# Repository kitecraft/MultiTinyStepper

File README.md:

# MCPStepper
PCB and Arduino library to control 4 unipolar stepper motors (28BYJ-48 typical)

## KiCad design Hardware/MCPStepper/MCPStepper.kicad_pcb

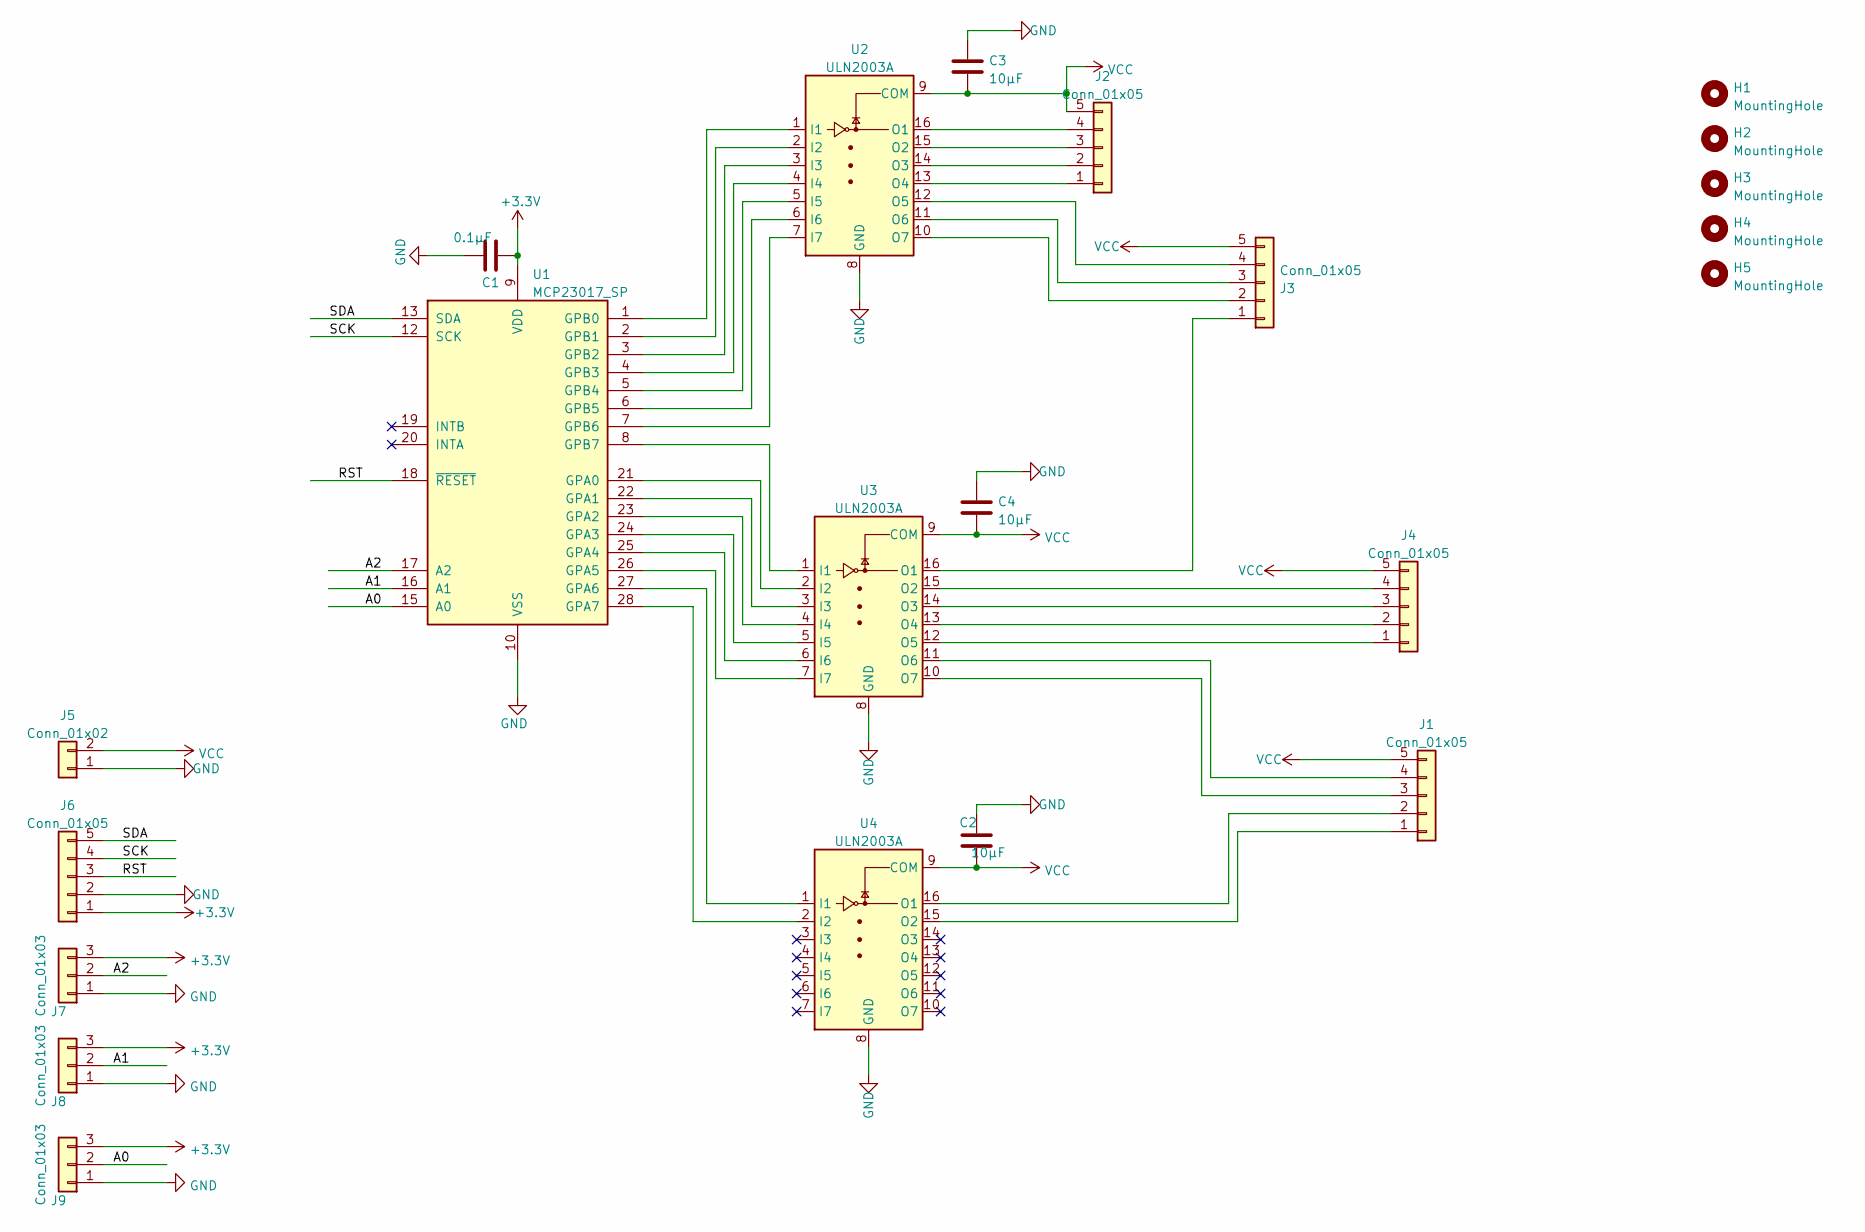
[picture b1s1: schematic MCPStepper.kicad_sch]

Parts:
C1: 0.1µF; C_Disc_D5.0mm_W2.5mm_P2.50mm
C2, C3, C4: 10µF; C_Disc_D5.0mm_W2.5mm_P2.50mm
H1, H2, H3, H4, H5: MountingHole; MountingHole_2.7mm
J1, J2, J3, J4: Conn_01x05; JST_XH_B5B-XH-A_1x05_P2.50mm_Vertical
J5: Conn_01x02; PinHeader_1x02_P2.54_Friction_Lock
J6: Conn_01x05; PinHeader_1x05_P2.54mm_Vertical
J7, J8, J9: Conn_01x03; PinHeader_1x03_P2.54mm_Vertical
U1: MCP23017_SP; DIP-28_W7.62mm_WithSocket
U2, U3, U4: ULN2003A; ULN2003 on Socket

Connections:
+3V3: C1.2, J6.1, J7.3, J8.3, J9.3, U1.9 (VDD)
/A0: J9.2, U1.15 (A0)
/A1: J8.2, U1.16 (A1)
/A2: J7.2, U1.17 (A2)
/RST: J6.3, U1.18 (~RESET)
/SCK: J6.4, U1.12 (SCK)
/SDA: J6.5, U1.13 (SDA)
GND: C1.1, C2.1, C3.1, C4.1, J5.1, J6.2, J7.1, J8.1, J9.1, U1.10 (VSS), U2.8 (GND), U3.8 (GND), U4.8 (GND)
unnamed: J3.1, U3.16 (O1)
unnamed: J3.2, U2.10 (O7)
unnamed: J3.3, U2.11 (O6)
unnamed: J3.4, U2.12 (O5)
unnamed: U1.1 (GPB0), U2.1 (I1)
unnamed: U1.2 (GPB1), U2.2 (I2)
unnamed: U1.3 (GPB2), U2.3 (I3)
unnamed: U1.4 (GPB3), U2.4 (I4)
unnamed: U1.5 (GPB4), U2.5 (I5)
unnamed: U1.6 (GPB5), U2.6 (I6)
unnamed: U1.7 (GPB6), U2.7 (I7)
unnamed: U1.8 (GPB7), U3.1 (I1)
unnamed: U1.21 (GPA0), U3.2 (I2)
unnamed: U1.22 (GPA1), U3.3 (I3)
unnamed: U1.23 (GPA2), U3.4 (I4)
unnamed: U1.24 (GPA3), U3.5 (I5)
unnamed: U1.25 (GPA4), U3.6 (I6)
unnamed: U1.26 (GPA5), U3.7 (I7)
unnamed: U1.27 (GPA6), U4.1 (I1)
unnamed: U1.28 (GPA7), U4.2 (I2)
unnamed: J2.1, U2.13 (O4)
unnamed: J2.2, U2.14 (O3)
unnamed: J2.3, U2.15 (O2)
unnamed: J2.4, U2.16 (O1)
unnamed: J1.3, U3.10 (O7)
unnamed: J1.4, U3.11 (O6)
unnamed: J4.1, U3.12 (O5)
unnamed: J4.2, U3.13 (O4)
unnamed: J4.3, U3.14 (O3)
unnamed: J4.4, U3.15 (O2)
unnamed: J1.1, U4.15 (O2)
unnamed: J1.2, U4.16 (O1)
VCC: C2.2, C3.2, C4.2, J1.5, J2.5, J3.5, J4.5, J5.2, U2.9 (COM), U3.9 (COM), U4.9 (COM)

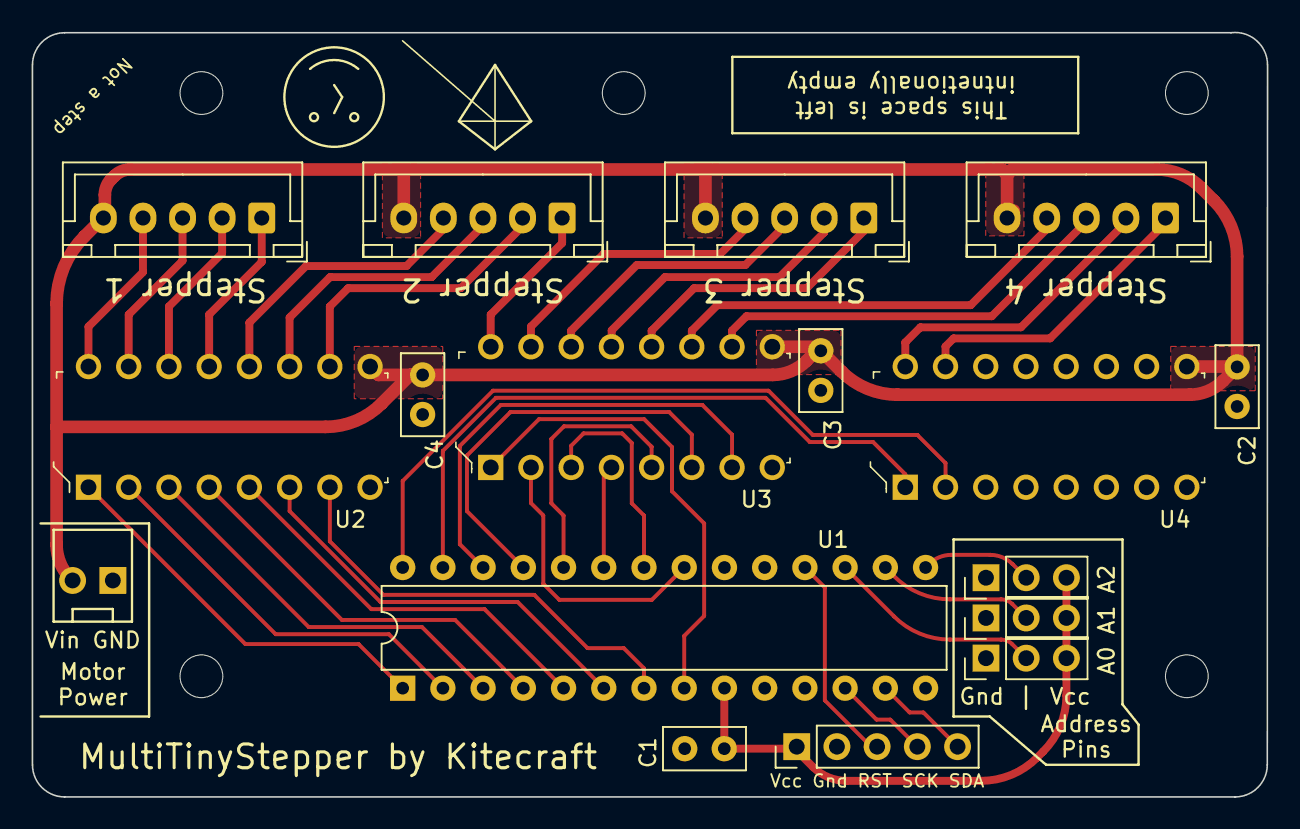
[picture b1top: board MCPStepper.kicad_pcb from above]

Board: 2 copper layers, 78.0 x 48.3 mm, 22 parts (0 on the bottom side), 41 nets.

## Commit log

2022-09-24 Initial hardware commit
2022-12-07 Many updates
2022-12-08 Much progress achieved.
2022-12-08 Updated the PCB
2022-12-09 Fixed bug for half stepping
2022-12-10 Working system.
2022-12-10 Add Arduino Library setup
2022-12-10 Add attribution for MCP23017 library.
2022-12-10 Fixed comment.
2022-12-10 Added comment for begin()
2022-12-10 Renamed example directory
2022-12-10 Moved to new folder
2022-12-10 Fixed includes for example
2022-12-11 PCB Updates
2023-01-26 Added reverse
2023-01-27 Add reverse option and reset pin
2023-01-28 Nearly complete I think.
